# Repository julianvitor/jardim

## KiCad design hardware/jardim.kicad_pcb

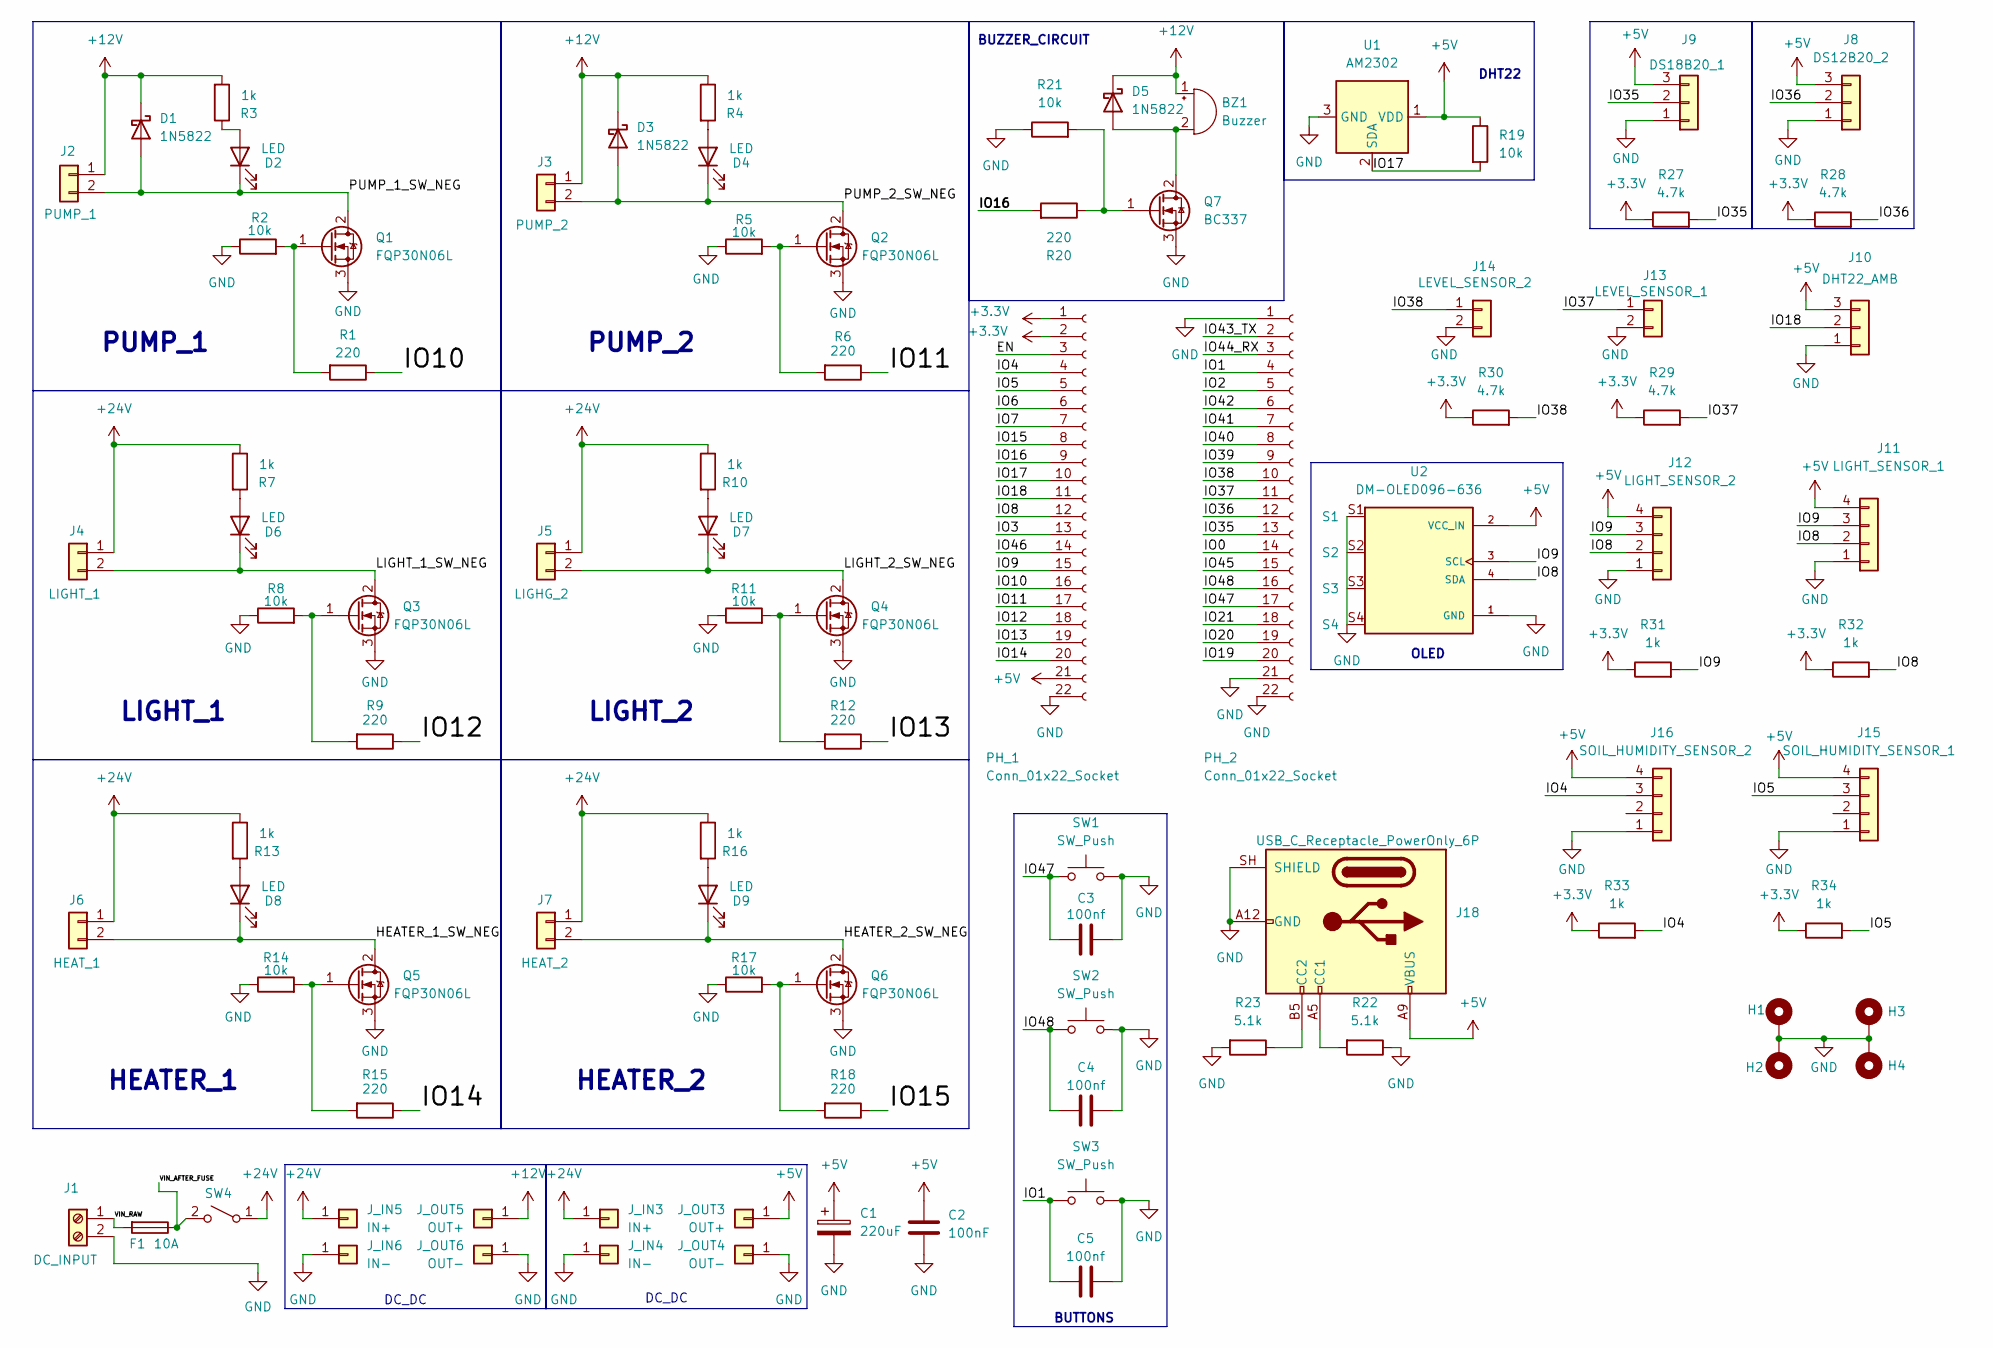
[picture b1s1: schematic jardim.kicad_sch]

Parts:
BZ1: Buzzer; Buzzer_12x9.5RM7.6
C1: 220uF; CP_Radial_D6.3mm_P2.50mm
C2: 100nF; C_Disc_D5.0mm_W2.5mm_P5.00mm
C3, C4, C5: 100nf; C_Disc_D3.0mm_W1.6mm_P2.50mm
D1, D3, D5: 1N5822; D_DO-201AD_P15.24mm_Horizontal
D2, D4, D6, D7, D8, D9: LED; LED_D5.0mm
F1: 10A; Fuseholder_Blade_Mini_Keystone_3568
H1, H2, H3, H4: MountingHole_Pad; MountingHole_3.2mm_M3_Pad_Via
J1: DC_INPUT; TerminalBlock_Phoenix_MKDS-1,5-2_1x02_P5.00mm_Horizontal
J2: PUMP_1; TerminalBlock_Phoenix_MKDS-1,5-2-5.08_1x02_P5.08mm_Horizont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
J3: PUMP_2; TerminalBlock_Phoenix_MKDS-1,5-2-5.08_1x02_P5.08mm_Horizont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
J4: LIGHT_1; TerminalBlock_Phoenix_MKDS-1,5-2-5.08_1x02_P5.08mm_Horizont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
J5: LIGHG_2; TerminalBlock_Phoenix_MKDS-1,5-2-5.08_1x02_P5.08mm_Horizont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
J6: HEAT_1; TerminalBlock_Phoenix_MKDS-1,5-2-5.08_1x02_P5.08mm_Horizont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
J7: HEAT_2; TerminalBlock_Phoenix_MKDS-1,5-2-5.08_1x02_P5.08mm_Horizont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
J8: DS12B20_2; JST_XH_B3B-XH-A_1x03_P2.50mm_Vertical
J9: DS18B20_1; JST_XH_B3B-XH-A_1x03_P2.50mm_Vertical
J10: DHT22_AMB; JST_XH_B3B-XH-A_1x03_P2.50mm_Vertical
J11: LIGHT_SENSOR_1; JST_XH_B4B-XH-A_1x04_P2.50mm_Vertical
J12: LIGHT_SENSOR_2; JST_XH_B4B-XH-A_1x04_P2.50mm_Vertical
J13: LEVEL_SENSOR_1; JST_XH_B2B-XH-A_1x02_P2.50mm_Vertical
J14: LEVEL_SENSOR_2; JST_XH_B2B-XH-A_1x02_P2.50mm_Vertical
J15: SOIL_HUMIDITY_SENSOR_1; JST_XH_B4B-XH-A_1x04_P2.50mm_Vertical
J16: SOIL_HUMIDITY_SENSOR_2; JST_XH_B4B-XH-A_1x04_P2.50mm_Vertical
J18: USB_C_Receptacle_PowerOnly_6P; USB_C_Receptacle_GCT_USB4125-xx-x_6P_TopMnt_Horizontal
J_IN3, J_IN5: IN+; TestPoint_Pad_3.0x3.0mm
J_IN4, J_IN6: IN-; TestPoint_Pad_3.0x3.0mm
J_OUT3, J_OUT5: OUT+; TestPoint_Pad_3.0x3.0mm
J_OUT4, J_OUT6: OUT-; TestPoint_Pad_3.0x3.0mm
PH_1, PH_2: Conn_01x22_Socket; PinSocket_1x22_P2.54mm_Vertical
Q1, Q2, Q3, Q4, Q5, Q6: FQP30N06L; TO-220-3_Vertical
Q7: BC337; TO-92_Inline_Horizontal2
R1, R6, R9, R12, R15, R18, R20: 220; R_Axial_DIN0207_L6.3mm_D2.5mm_P10.16mm_Horizontal
R2, R5, R8, R11, R14, R17, R21: 10k; R_Axial_DIN0207_L6.3mm_D2.5mm_P10.16mm_Horizontal
R3, R4, R7, R10, R13, R16: 1k; R_Axial_DIN0207_L6.3mm_D2.5mm_P10.16mm_Horizontal
R19: 10k; R_Axial_DIN0207_L6.3mm_D2.5mm_P7.62mm_Horizontal
R22, R23: 5.1k; R_Axial_DIN0207_L6.3mm_D2.5mm_P10.16mm_Horizontal
R27, R28, R29, R30: 4.7k; R_Axial_DIN0207_L6.3mm_D2.5mm_P7.62mm_Horizontal
R31, R32, R33, R34: 1k; R_Axial_DIN0207_L6.3mm_D2.5mm_P7.62mm_Horizontal
SW1, SW2, SW3: SW_Push; SW_PUSH_6mm
SW4: SW_SPST; TerminalBlock_Phoenix_MKDS-1,5-2-5.08_1x02_P5.08mm_Horizont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
U1: AM2302; ASAIR_AM2302_P2.54mm_Vertical
U2: DM-OLED096-636; MODULE_DM-OLED096-636; PARTREV 2018-09-10

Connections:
+3.3V: PH_1.1, PH_1.2, R27.1, R28.1, R29.1, R30.1, R31.1, R32.1, R33.1, R34.1
+5V: C1.1, C2.1, J8.3, J9.3, J10.3, J11.4, J12.4, J15.4, J16.4, J18.A9 (VBUS), J18.B9 (VBUS), J_OUT3.1 (Pin_1_1), PH_1.21, R19.1, U1.1 (VDD), U2.2 (VCC_IN)
+12V: BZ1.1 (+), D1.1 (K), D3.1 (K), D5.1 (K), J2.1, J3.1, J_OUT5.1 (Pin_1_1), R3.2, R4.1
+24V: J4.1, J5.1, J6.1, J7.1, J_IN3.1 (Pin_1_1), J_IN5.1 (Pin_1_1), R7.1, R10.1, R13.1, R16.1, SW4.1 (A)
/EN: PH_1.3
/HEATER_1_SW_NEG: D8.1 (K), J6.2, Q5.2 (D)
/HEATER_2_SW_NEG: D9.1 (K), J7.2, Q6.2 (D)
/IO0: PH_2.14
/IO1: C5.2, PH_2.4, SW3.1
/IO2: PH_2.5
/IO3: PH_1.13
/IO4: J16.3, PH_1.4, R33.2
/IO5: J15.3, PH_1.5, R34.2
/IO6: PH_1.6
/IO7: PH_1.7
/IO8: J11.2, J12.2, PH_1.12, R32.2, U2.4 (SDA)
/IO9: J11.3, J12.3, PH_1.15, R31.2, U2.3 (SCL)
/IO10: PH_1.16, R1.1
/IO11: PH_1.17, R6.1
/IO12: PH_1.18, R9.1
/IO13: PH_1.19, R12.1
/IO14: PH_1.20, R15.1
/IO15: PH_1.8, R18.1
/IO16: PH_1.9, R20.2
/IO17: PH_1.10, R19.2, U1.2 (SDA)
/IO18: J10.2, PH_1.11
/IO19: PH_2.20
/IO20: PH_2.19
/IO21: PH_2.18
/IO35: J9.2, PH_2.13, R27.2
/IO36: J8.2, PH_2.12, R28.2
/IO37: J13.1, PH_2.11, R29.2
/IO38: J14.1, PH_2.10, R30.2
/IO39: PH_2.9
/IO40: PH_2.8
/IO41: PH_2.7
/IO42: PH_2.6
/IO43_TX: PH_2.2
/IO44_RX: PH_2.3
/IO45: PH_2.15
/IO46: PH_1.14
/IO47: C3.2, PH_2.17, SW1.1
/IO48: C4.2, PH_2.16, SW2.1
/LIGHT_1_SW_NEG: D6.1 (K), J4.2, Q3.2 (D)
/LIGHT_2_SW_NEG: D7.1 (K), J5.2, Q4.2 (D)
/PUMP_1_SW_NEG: D1.2 (A), D2.1 (K), J2.2, Q1.2 (D)
/PUMP_2_SW_NEG: D3.2 (A), D4.1 (K), J3.2, Q2.2 (D)
/VIN_AFTER_FUSE: F1.1, SW4.2 (B)
/VIN_RAW: F1.2, J1.1
GND: C1.2, C2.2, C3.1, C4.1, C5.1, H1.1 (1_1), H2.1 (1_1), H3.1 (1_1), H4.1 (1_1), J1.2, J8.1, J9.1, J10.1, J11.1, J12.1, J13.2, J14.2, J15.1, J16.1, J18.A12 (GND), J18.B12 (GND), J18.SH (SHIELD), J_IN4.1 (Pin_1_1), J_IN6.1 (Pin_1_1), J_OUT4.1 (Pin_1_1), J_OUT6.1 (Pin_1_1), PH_1.22, PH_2.1, PH_2.21, PH_2.22, Q1.3 (S), Q2.3 (S), Q3.3 (S), Q4.3 (S), Q5.3 (S), Q6.3 (S), Q7.3 (S), R2.1, R5.1, R8.1, R11.1, R14.1, R17.1, R21.1, R22.1, R23.2, SW1.2, SW2.2, SW3.2, U1.3 (GND), U1.4 (GND), U2.1 (GND)
unnamed: BZ1.2 (-), D5.2 (A), Q7.2 (D)
unnamed: D2.2 (A), R3.1
unnamed: D4.2 (A), R4.2
unnamed: D6.2 (A), R7.2
unnamed: D7.2 (A), R10.2
unnamed: D8.2 (A), R13.2
unnamed: D9.2 (A), R16.2
unnamed: J18.A5 (CC1), R22.2
unnamed: J18.B5 (CC2), R23.1
unnamed: Q1.1 (G), R1.2, R2.2
unnamed: Q2.1 (G), R5.2, R6.2
unnamed: Q3.1 (G), R8.2, R9.2
unnamed: Q4.1 (G), R11.2, R12.2
unnamed: Q5.1 (G), R14.2, R15.2
unnamed: Q6.1 (G), R17.2, R18.2
unnamed: Q7.1 (G), R20.1, R21.2

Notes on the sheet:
HEATER_1
DC_DC
OLED
BUZZER_CIRCUIT
LIGHT_2
PUMP_1
DHT22
LIGHT_1
HEATER_2
BUTTONS
PUMP_2

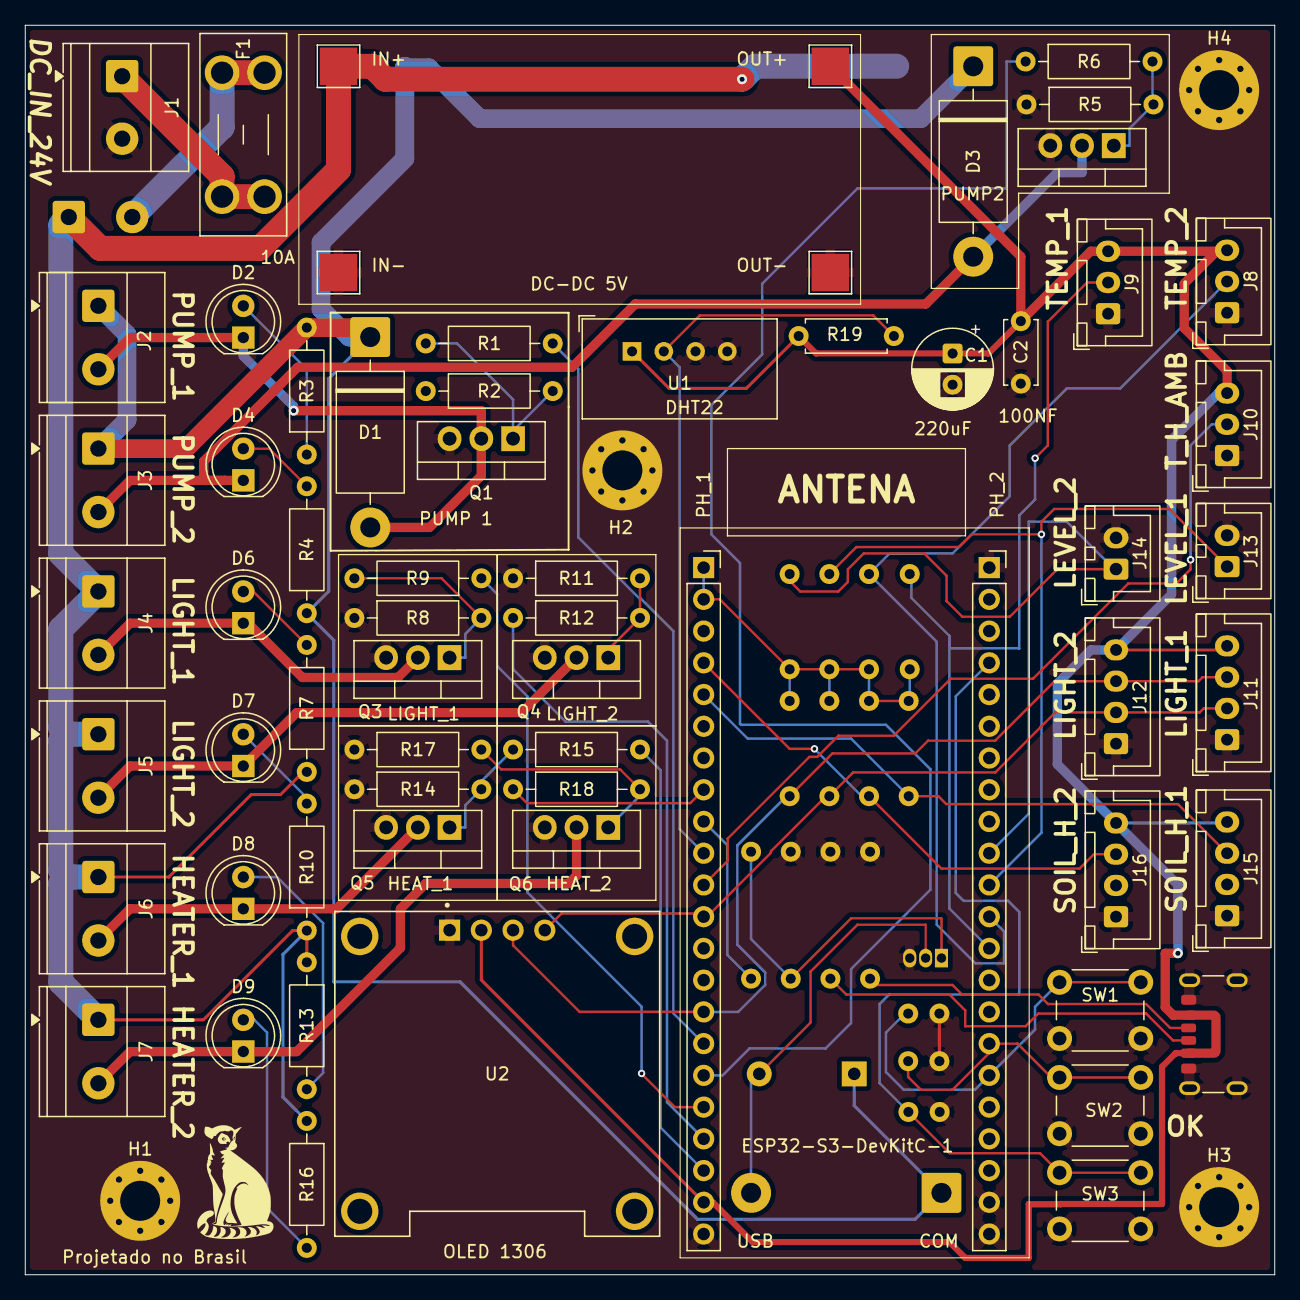
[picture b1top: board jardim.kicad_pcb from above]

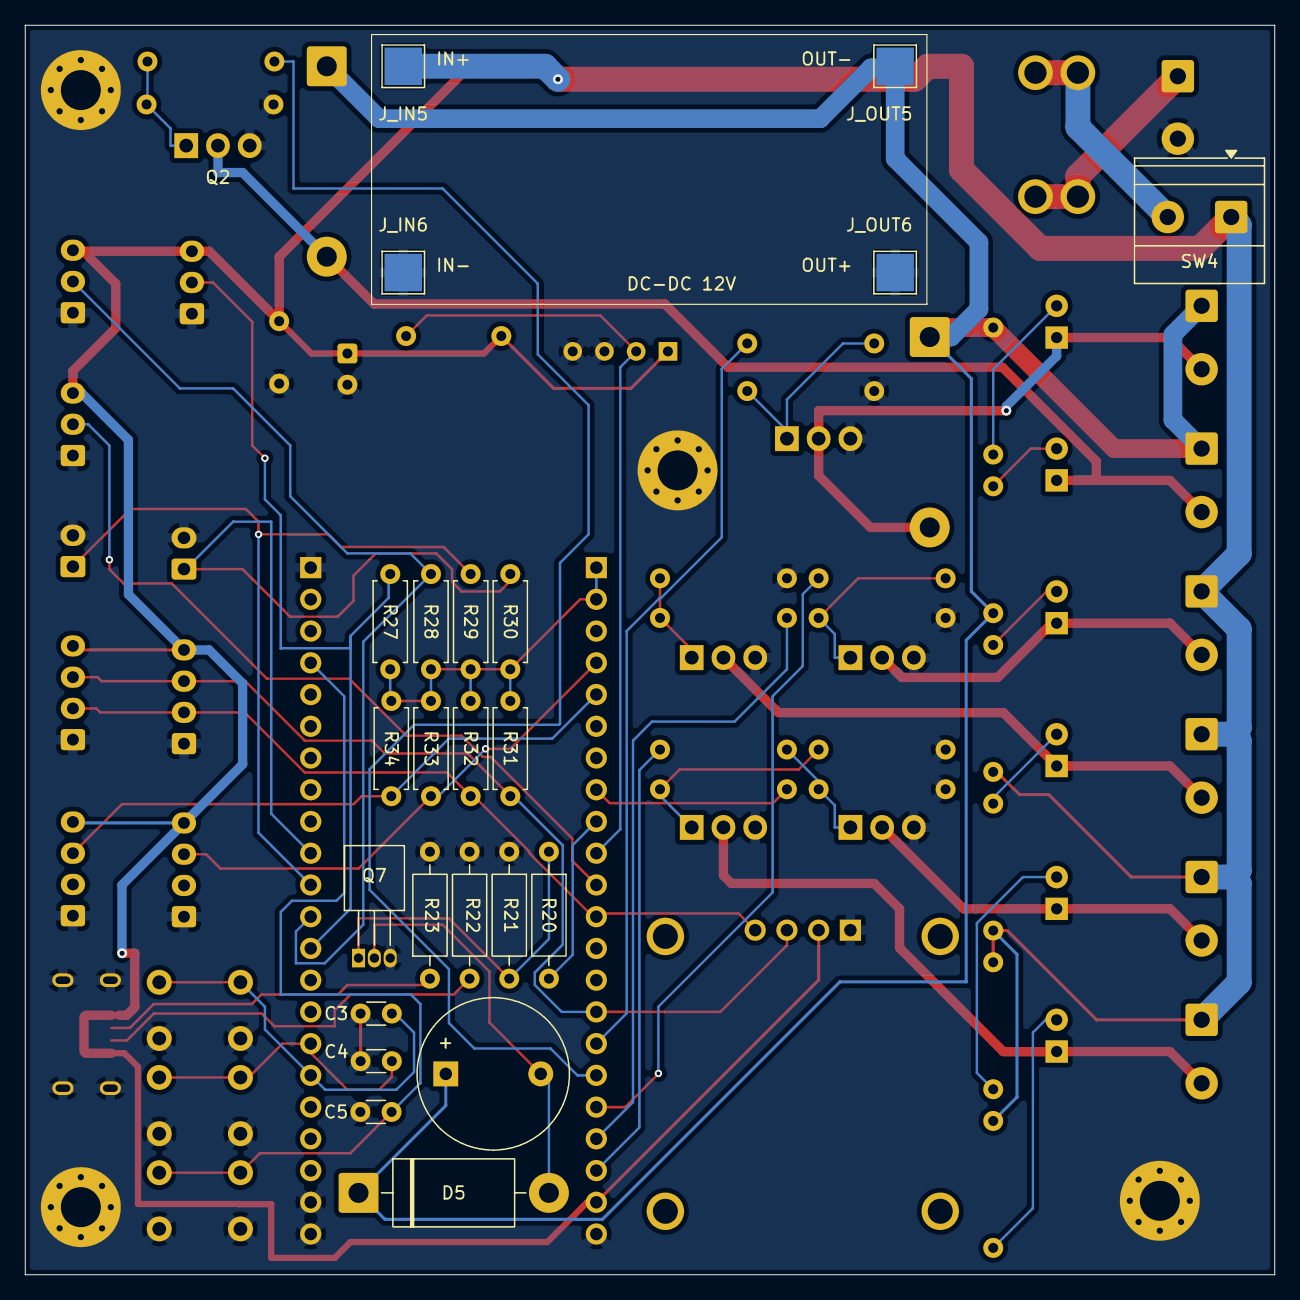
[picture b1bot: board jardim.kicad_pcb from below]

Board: 2 copper layers, 100.0 x 100.0 mm, 91 parts (23 on the bottom side), 49 nets.

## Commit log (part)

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2023-09-16 repo migration
2023-09-16 readme
2023-09-16 new dockerfile and startup with correct repo
2023-09-17 co2, light, new endpoints
2023-09-17 botão de rega, icone de seta ocultar dados com h2, (push no repo antigo, correção agora)
2023-09-17 contraste nos botoes
2023-09-17 new min
2023-09-17 again
2023-09-21 refatorando app.py
2023-09-22 apenas spa, diretorio para resposta de erro
2023-09-22 unittest rotas
2023-09-22 novo js
2023-09-22 script poo com a invocação correta do preferredLanguage
2023-09-22 script js refatorado é o padrao
2023-09-22 404 httpcats
2023-12-13 removida a função de idioma dinamico, estilo pagina login e pagina login
2023-12-13 teste rota /login, refino dark mode e botão switch
2023-12-13 separando os dados da dashboard
2023-12-13 lista sensores eletricidade e reservatorio
2023-12-13 water buttton ok, 3 dados separados e pagina de cadastro
2023-12-13 width div central
2023-12-14 pagina de apresentação, validação de formulario de cadastro minima
2023-12-14 gunicorn
2023-12-14 guincorn requirements
2023-12-14 separando front em flask e rotas em fast api, rota sensores e regar
2023-12-14 Cors no fastapi, script apontando para api, fix bugs rotas fastapi
2023-12-14 testes do front flask
2023-12-14 testes de front e back, dockerfile e configuração de containers
2023-12-14 docker file com variavel de ambiente corretamente especificada
2023-12-14 portas certas
2023-12-14 aceitando todos os ips no uvicorn
2023-12-14 organizando os diretorios
2023-12-23 mudança no script de inicialização e portas
2023-12-26 cors wsl
2023-12-27 windows.location.hostname
2023-12-27 separando o serviço do endpoint /sensor-data
2023-12-28 startup matando processos antes
2023-12-28 adeus gatway, olá serviço regar
2023-12-28 adicioar serviços ao startup.sh
2023-12-28 serviço de gerenciamento com uma função proxy para os dados de cidade
2023-12-28 Estilo nos botoes
2023-12-28 organização de pastas
2023-12-28 resolvendo as importações e refatorando o teste para microserviços
2023-12-28 requirements.txt
2023-12-28 adicionando caminho para o python encontrar modulos
2023-12-28 removendo o link javascript do index.html
2024-01-01 serviço cadastro basico, validação e sanitização
2024-01-01 teste de cadastro, adicionar mais regras de validação e tipo de dados certo
2024-01-01 front consumindo a api cadastro
2024-01-01 mudando as respospostas em details de cadastro, front end com repita a senha
2024-01-01 serviço cadastro com banco de dados
2024-01-01 criar tabela de testes e ajustes de importação
2024-01-01 bad request cadastro repetido, teste cidade e cadastro existente
2024-01-02 arquivo darkmode
2024-01-02 arquivo cadastro.js refeito do zero
2024-01-02 apagando alguns textos
2024-01-02 pool de conexoes no cadastro
2024-01-02 função verificar instalação shellscript
2024-01-03 mudando o endereço rotas serviços para evitar conflitos
2024-01-04 on_event -> event_handler
2024-01-04 rota login, sanitizar e validar
2024-01-04 login -> busca no banco, validação, comparação + SH
2024-01-05 integrando o front na api
2024-01-05 organizando estetica do codigo, redirecionando login > dashboard
2024-01-05 sai fora Ç
2024-01-06 responder acess token
2024-01-06 função ocultar managment dentro do app
2024-01-06 sensorER e sensorES no gardenAPP
2024-01-07 refatorar event handler cadastro
2024-01-08 pelejando com testes, passando url do banco pelo main do serviço
2024-01-08 ainda apanhando dos testes, mas agora do pytest
2024-01-08 teste openAI
2024-03-11 requirements completo e startup na raiz
2024-03-11 conflito jtw e pyjtw, cors no flask
2024-12-25 script startup com autenticacao do DB
2026-01-03 Initial plan
2026-01-03 Add comprehensive .gitignore for Go + Tailwind CSS project
2026-01-03 Fix duplicate pattern and improve macOS Icon ignore
2026-01-03 esqueleto do projeto
2026-01-04 docker
